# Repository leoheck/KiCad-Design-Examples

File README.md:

# KiCad Design Examples

This repository contains KiCad circuit designs created in an effort to highlight some aspects of KiCad features and their practical use for various types of circuit design. 

## [DEX_MRHW0000 - basic line filter](dex0000_mains_filter/readme.md) 

A simple line filter circuit implements individual clearances for phase-to-neutral, mains-to-earth, and earth to PCB edge, as well as small self-clearance for nets that share the same DC potential, but may be split to account for AC behavior, in this case of a common-mode choke.

---

**Corrections and Improvements**

Feedback is always welcome.

**Legal Disclaimer**

All files are provided as-is. Physical realization of any circuit requires design review and appropriate selection of components. Operation may require connection to mains or other power sources but the designs themselves do not provide or describe adequate protection against electrical shock and fire hazards. No responsibilities for damage or harm caused by use of material presented herein will be accepted.

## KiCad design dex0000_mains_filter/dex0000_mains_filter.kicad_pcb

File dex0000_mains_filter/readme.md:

# DEX_MRHW0000 - basic line filter

A simple line filter circuit implements individual clearances for phase-to-neutral, mains-to-earth, and earth to PCB edge clearances, as well as small self-clearances for nets that share the same DC potential, but may be split to account for AC behavior. The latter is applied hier to the case of a common-mode choke.

## Schematic

## Net Classes

The Net Classes panel is used to 

- declare net class names, 
- set basic net class values and
- assign each net in the schematic a class.

Clearance values given here can be superseded by rules written in Design Rules > Rules.

## Clearance Rules

When specifying only a basic clearance value in the Net Classes table, this value becomes the distance any net item (track segment, pad, ...) must keep  form items in other nets, no matter the net class. Between two items of net classes with differing clearance requirements, the larger clearance is applied. 

An equivalent rule for class_x with 0.2mm clearance has the form

	(rule "class_X"
	    (condition "A.NetClass == 'class_X'")
	    (constraint clearance (min 0.2mm)))

Such a rule written in Design Rules > Rules supersedes the implicit definition through the Net Classes table, but is functionally equivalent until the boolean expression it contains is extended. Meanwhile, the Net Classes table values cover all cases not otherwise described in the design rules script.

The distinction between same-class net and other-class net clearances is made by forming two complementary rules. A and B are the corresponding board items between which the clearance resolution is determined. 

	(rule "N_mutual_clearance"
	    (condition "A.NetClass == 'class_N' && B.NetClass != A.NetClass")
	    (constraint clearance (min 3.0mm)))
	
	(rule "N_self_clearance"
	    (condition "A.NetClass == 'class_N' && B.NetClass == A.NetClass")
	    (constraint clearance (min 0.75mm)))

Finally, order-of-evaluation needs to be kept in mind. In the example below, clearance rules named r1-r6 for short are thought to be written in consecutive order, which leads to a chevron stack pattern in the associated clearance matrix. r1, r3, r5 are mutual clearance rules, r2, r4, r6 are same-class clearance rules:

	step 1:					step 2:					step 3:
		X	Y	Z			X	Y	Z			X	Y	Z
	X		r1	r1		X	r2	r1	r1		X	r2	r3	r1
	Y	r1				Y	r1				Y	r3		r3	
	Z	r1				Z	r1				Z	r1	r3	

	step 4:					step 5:					step 6:
		X	Y	Z			X	Y	Z			X	Y	Z
	X	r2	r3	r1		X	r2	r3	r5		X	r2	r3	r5
	Y	r3	r4	r3		Y	r3	r4	r5		Y	r3	r4	r5	
	Z	r1	r3			Z	r5	r5			Z	r5	r5	r6

The roles of A and B in the rule description can be swapped, which makes the clearance matrix symmetric, so it's usually only given in triangle form. 

In its most general form, clearance matrix elements can also be specified individually by writing out all (N²+N)/2 combinations of N net classes occuring in the design, including the diagonal ones:

	(rule "clearance_<class_i>_<class_j>"
	    (condition "A.NetClass == '<class_i>' && A.NetClass == '<class_j>'")
	    (constraint clearance (min 0.2mm)))

where <class_i>, <class_j> are placeholders. 

### Rules validation

Design Rules can also describe constraints with respect to net classes not (yet) contained in the design. This may at a later stage be pointed out in the form of syntax check info messages. Always validate the correctness of the resulting clearances, for example by selecting two layout items and using Inspect > Clearance Resolution to see which rule and what clearance value was found to apply.

### Clearance Rules For This Design

Please see the project files for the full list of rules. An excerpt is given below.

    # Project Rules
    #
    # Phase is segmented to insert a fuse holder and one winding of a common-mode filter choke.
    # A spark gap is inserted across the filter winding to prevent insulation breakdown in 
    # the event of a transient overvoltage condition. The same concept is applied to neutral.
    #
    # Clearance Matrix equivalent:
    #
    #			class_L		class_N		class_PE
    #	class_L		0.75mm		3.0mm		4.5mm
    #	class_N				0.75mm		4.5mm
    #	class_PE					0.2mm*
    #
    # * Note there is only PE_mutual_clearance for clearance to other nets, so class_PE self-clearance
    #   defaults to 0.2mm from Project > Net Classes.

## Net Class Inspection

All members of a net class can be highlighted by using the right-click option "Hightlight nets in <class>" of a class listed in Appearance > Nets > Net Classes: 

---
This project is part of a set of design examples. See [https://github.com/MisterHW/KiCad-Design-Examples/](https://github.com/MisterHW/KiCad-Design-Examples/) for more.

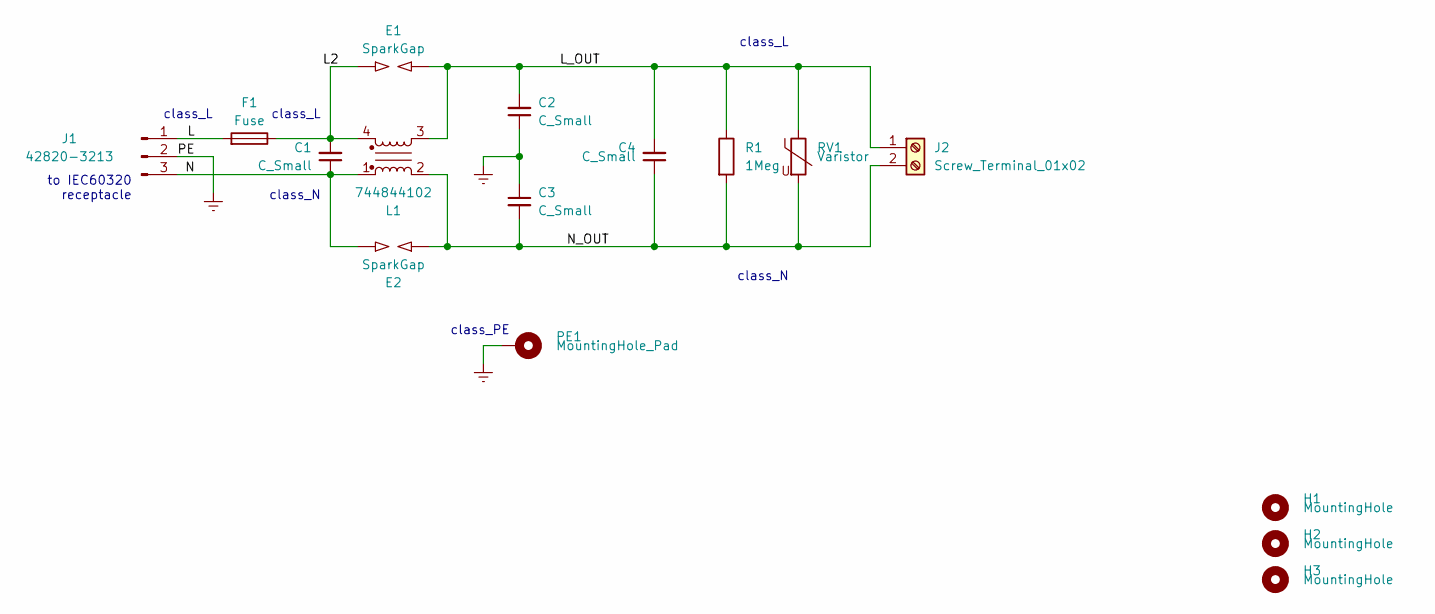
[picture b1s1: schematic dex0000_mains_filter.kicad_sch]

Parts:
C1, C4: C_Small; C_Rect_L18.0mm_W8.0mm_P15.00mm_FKS3_FKP3
C2, C3: C_Small; C_Disc_D9.0mm_W5.0mm_P10.00mm
E1, E2: SparkGap; SG1210
F1: Fuse; Fuseholder_Cylinder-5x20mm_Schurter_FAB_0031-355x_Horizonta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
H1, H2, H3: MountingHole; MountingHole_4.3mm_M4_DIN965
J1: 42820-3213; Molex_Mini-Fit_Sr_42820-32XX_1x03_P10.00mm_Horizontal_Therm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
J2: Screw_Terminal_01x02; TerminalBlock_MetzConnect_Type171_RT13702HBWC_1x02_P7.50mm_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
L1: 744844102; WE-ExB
PE1: MountingHole_Pad; MountingHole_4.3mm_M4_Pad_Via
R1: 1Meg; R_Axial_DIN0414_L11.9mm_D4.5mm_P15.24mm_Horizontal
RV1: Varistor; RV_Disc_D12mm_W4.2mm_P7.5mm

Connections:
/L: F1.2, J1.1
/L2: C1.2, E1.1, F1.1, L1.4
/L_OUT: C2.2, C4.2, E1.2, J2.1, L1.3, R1.1, RV1.1
/N: C1.1, E2.1, J1.3, L1.1
/N_OUT: C3.2, C4.1, E2.2, J2.2, L1.2, R1.2, RV1.2
Earth: C2.1, C3.1, J1.2, PE1.1

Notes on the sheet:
to IEC60320 receptacle
class_L
class_N
class_PE

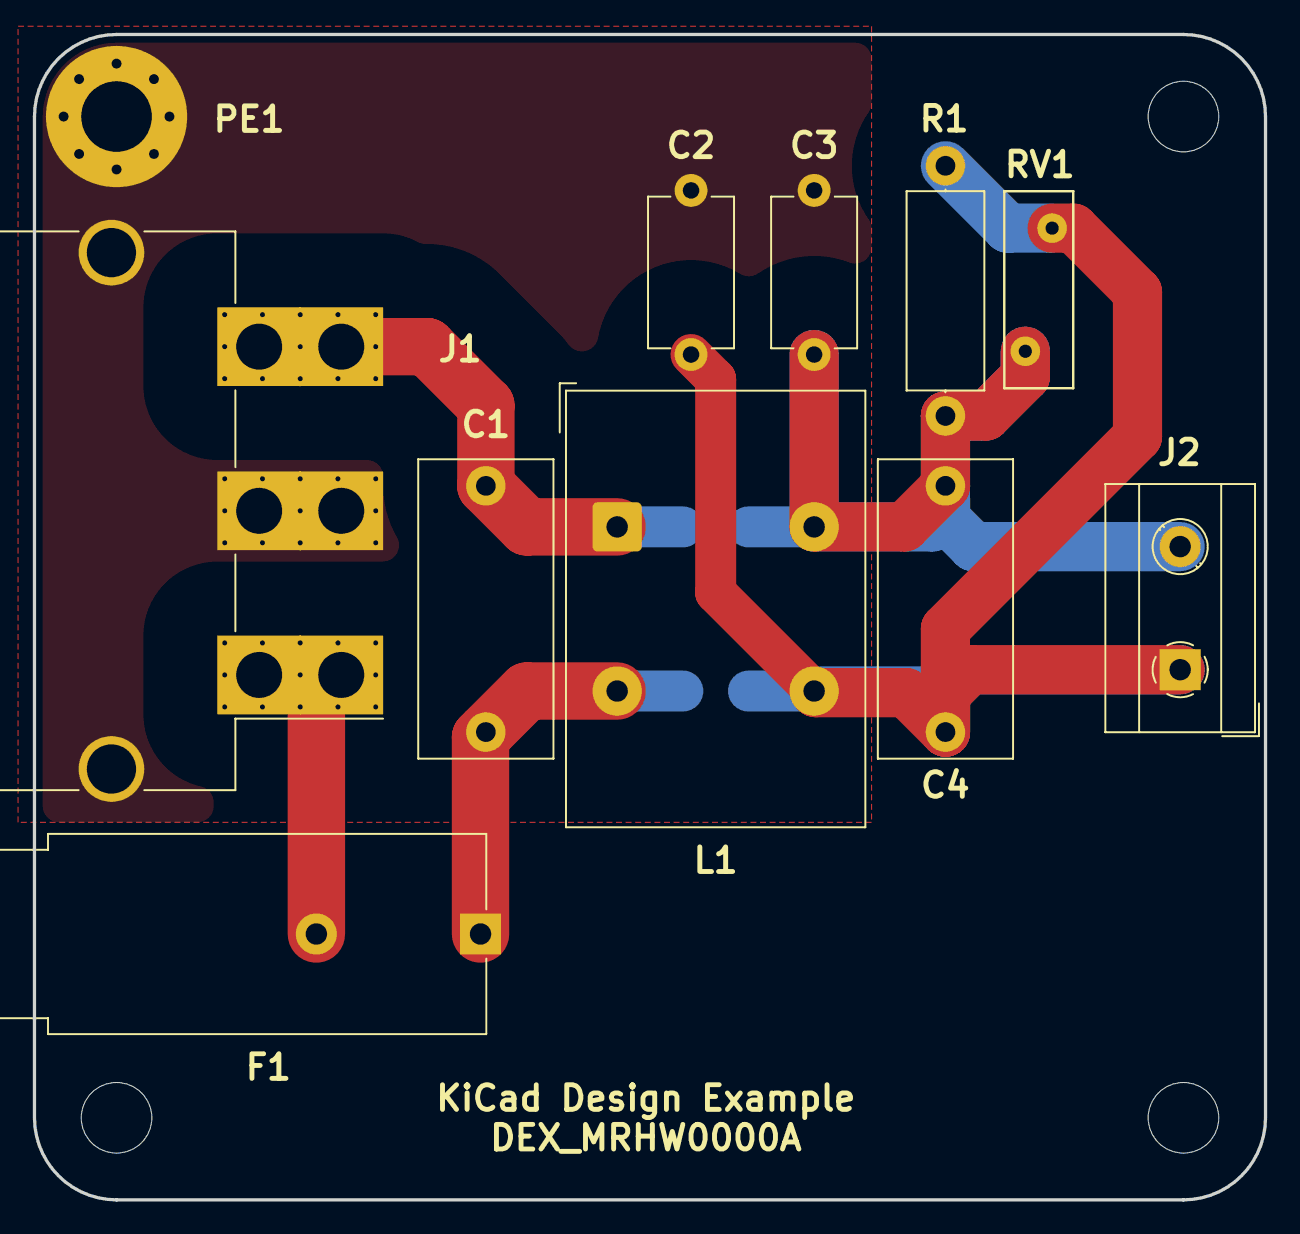
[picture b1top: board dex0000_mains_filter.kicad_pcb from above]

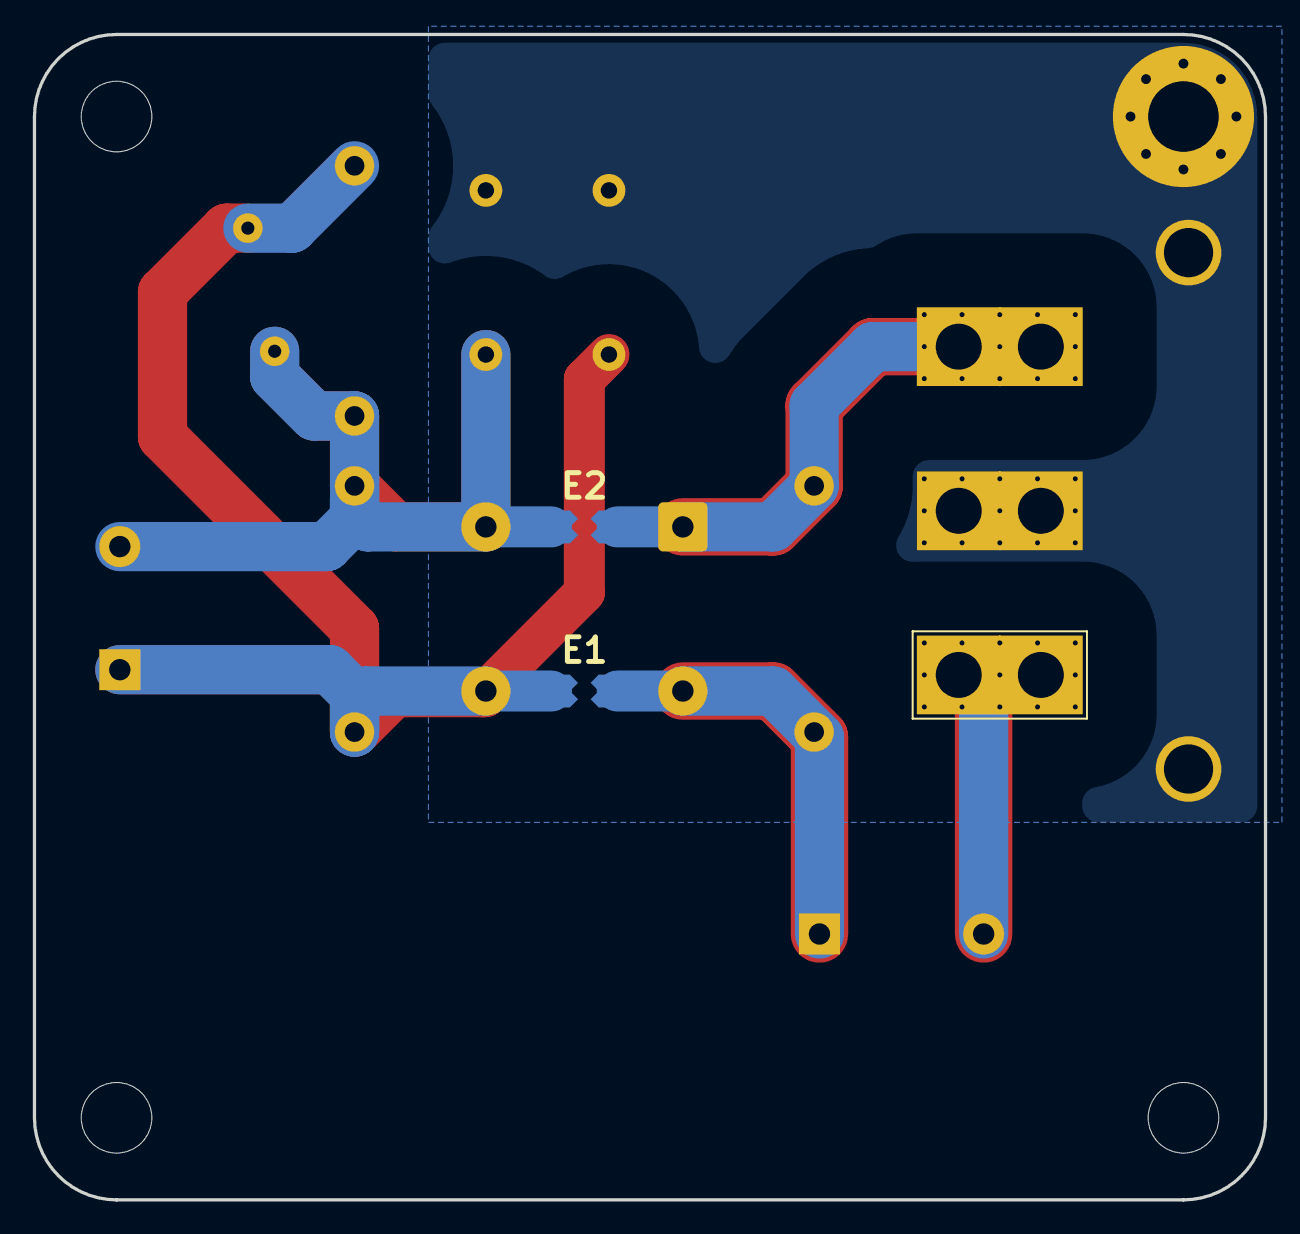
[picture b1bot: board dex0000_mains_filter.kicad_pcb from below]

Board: 2 copper layers, 75.0 x 71.0 mm, 16 parts (2 on the bottom side), 6 nets.

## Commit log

2020-10-03 Add files via upload
    KiCad Design Example DEX0000A: mains filter with WE-ExB common-mode choke highlights clearance definitions via design rules.
2020-10-04 Add files via upload
    updated design with documentation. Fixes 3.0mm self-clearances (now 0.75mm)
2020-10-04 Update readme.md
    modified indentation for readability on github
2020-10-06 Replace tabs with spaces
    So the table will be always formatted no matter the text editor.
